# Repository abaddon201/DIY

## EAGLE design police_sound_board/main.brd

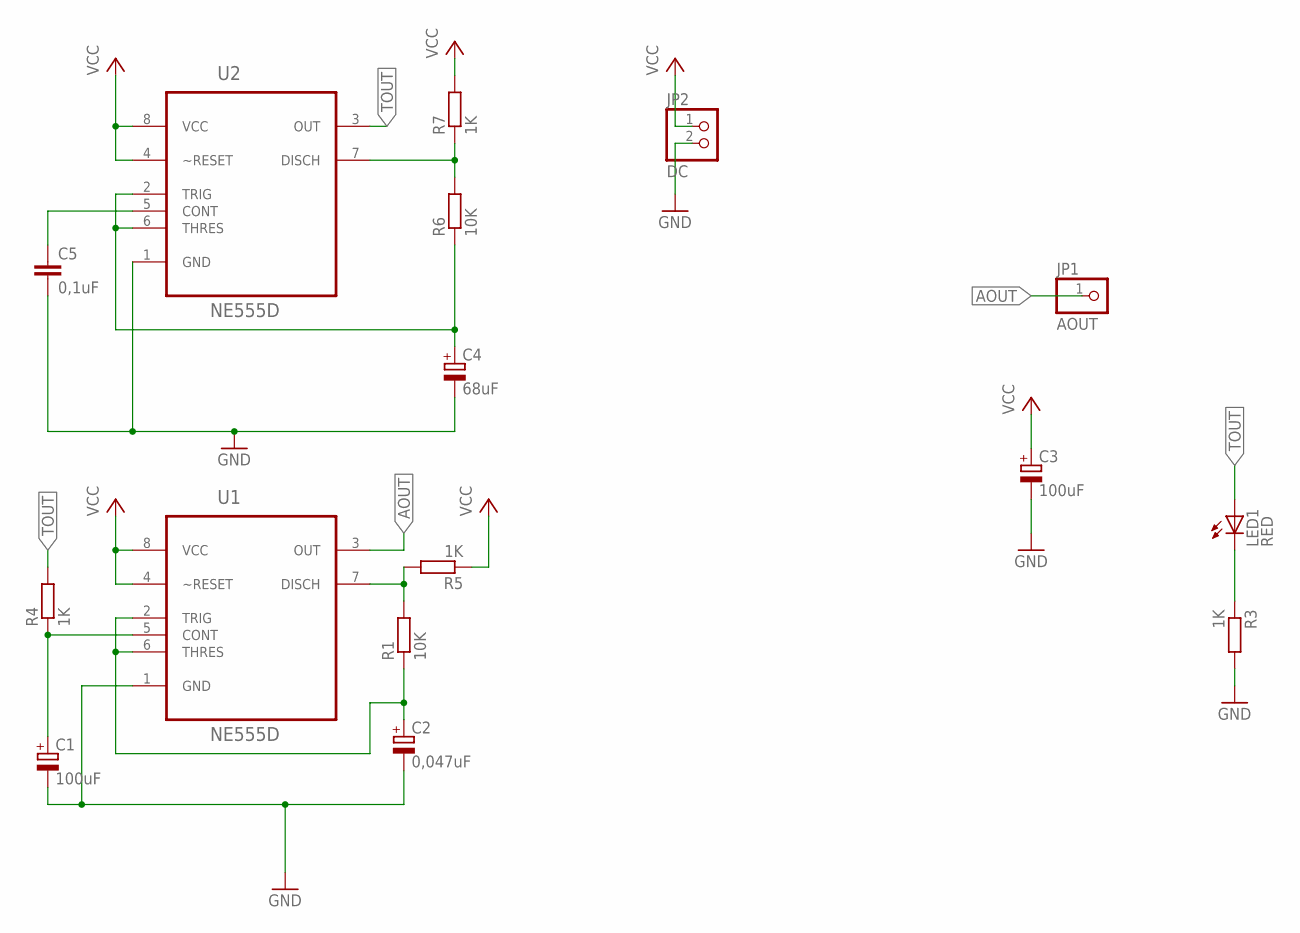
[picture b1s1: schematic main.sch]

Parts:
C1, C3: 100uF; E3,5-8
C2: 0,047uF; E3,5-8
C4: 68uF; E3,5-8
C5: 0,1uF; C025-025X050
JP1: AOUT; 1X01
JP2: DC; 1X02
LED1: RED; CHIPLED_0805
R1, R6: 10K; R0805
R3, R4, R5, R7: 1K; R0805
U1, U2: NE555D; SOIC127P600X175-8N

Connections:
AOUT: JP1.1, U1.3 (OUT)
GND: C1.-, C2.-, C3.-, C4.-, C5.2, JP2.2, R3.2, U1.1 (GND), U2.1 (GND)
unnamed: R1.2, R5.2, U1.7 (DISCH)
unnamed: C5.1, U2.5 (CONT)
unnamed: C2.+, R1.1, U1.2 (TRIG), U1.6 (THRES)
unnamed: C1.+, R4.1, U1.5 (CONT)
unnamed: R6.2, R7.1, U2.7 (DISCH)
unnamed: LED1.C, R3.1
unnamed: C4.+, R6.1, U2.2 (TRIG), U2.6 (THRES)
TOUT: LED1.A, R4.2, U2.3 (OUT)
VCC: C3.+, JP2.1, R5.1, R7.2, U1.4 (~RESET), U1.8 (VCC), U2.4 (~RESET), U2.8 (VCC)

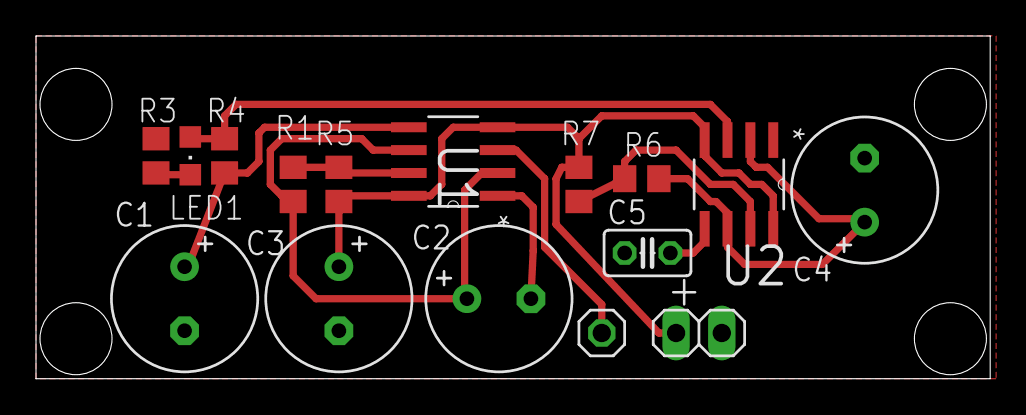
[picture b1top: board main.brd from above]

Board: 2 copper layers, 53.0 x 19.0 mm, 16 parts (0 on the bottom side), 11 nets.

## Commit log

2016-05-11 moved to english named folder
2016-05-11 removed speaker, added AOUT pin, added power connector pins
2016-05-12 added + sign for DC connector
2020-09-09 added zx
2020-09-10 updated power lines
2020-09-11 upadted connectors
2020-09-12 update devboard routing
2020-09-15 added memory devboard, moved devboard to schematic
2020-09-15 updated board and notes
2020-09-15 updated docs
2020-09-16 updated focs, added Z80 devboard
2020-09-17 added ZX Keyboard
2020-09-17 reorganized folders
2020-09-18 reorganizing. finished ram and keyboard, updated z80
2020-09-18 repo reoganise
2020-09-18 fixed keyboard
2020-09-18 updated ram 128k, 512k, keyboard
2020-09-18 some reordering in the main project
2020-09-18 updated schemes
2020-09-19 added AY devboard
2020-09-19 added tape in devboard
2020-09-19 updated BOM
2020-09-19 bom updates
2020-09-19 tap2wav
2020-09-22 added z80 pdip. updated all boards
2020-10-12 fixed 496 devboard
    fixed tracks for oscillators
2022-03-04 pentagon
